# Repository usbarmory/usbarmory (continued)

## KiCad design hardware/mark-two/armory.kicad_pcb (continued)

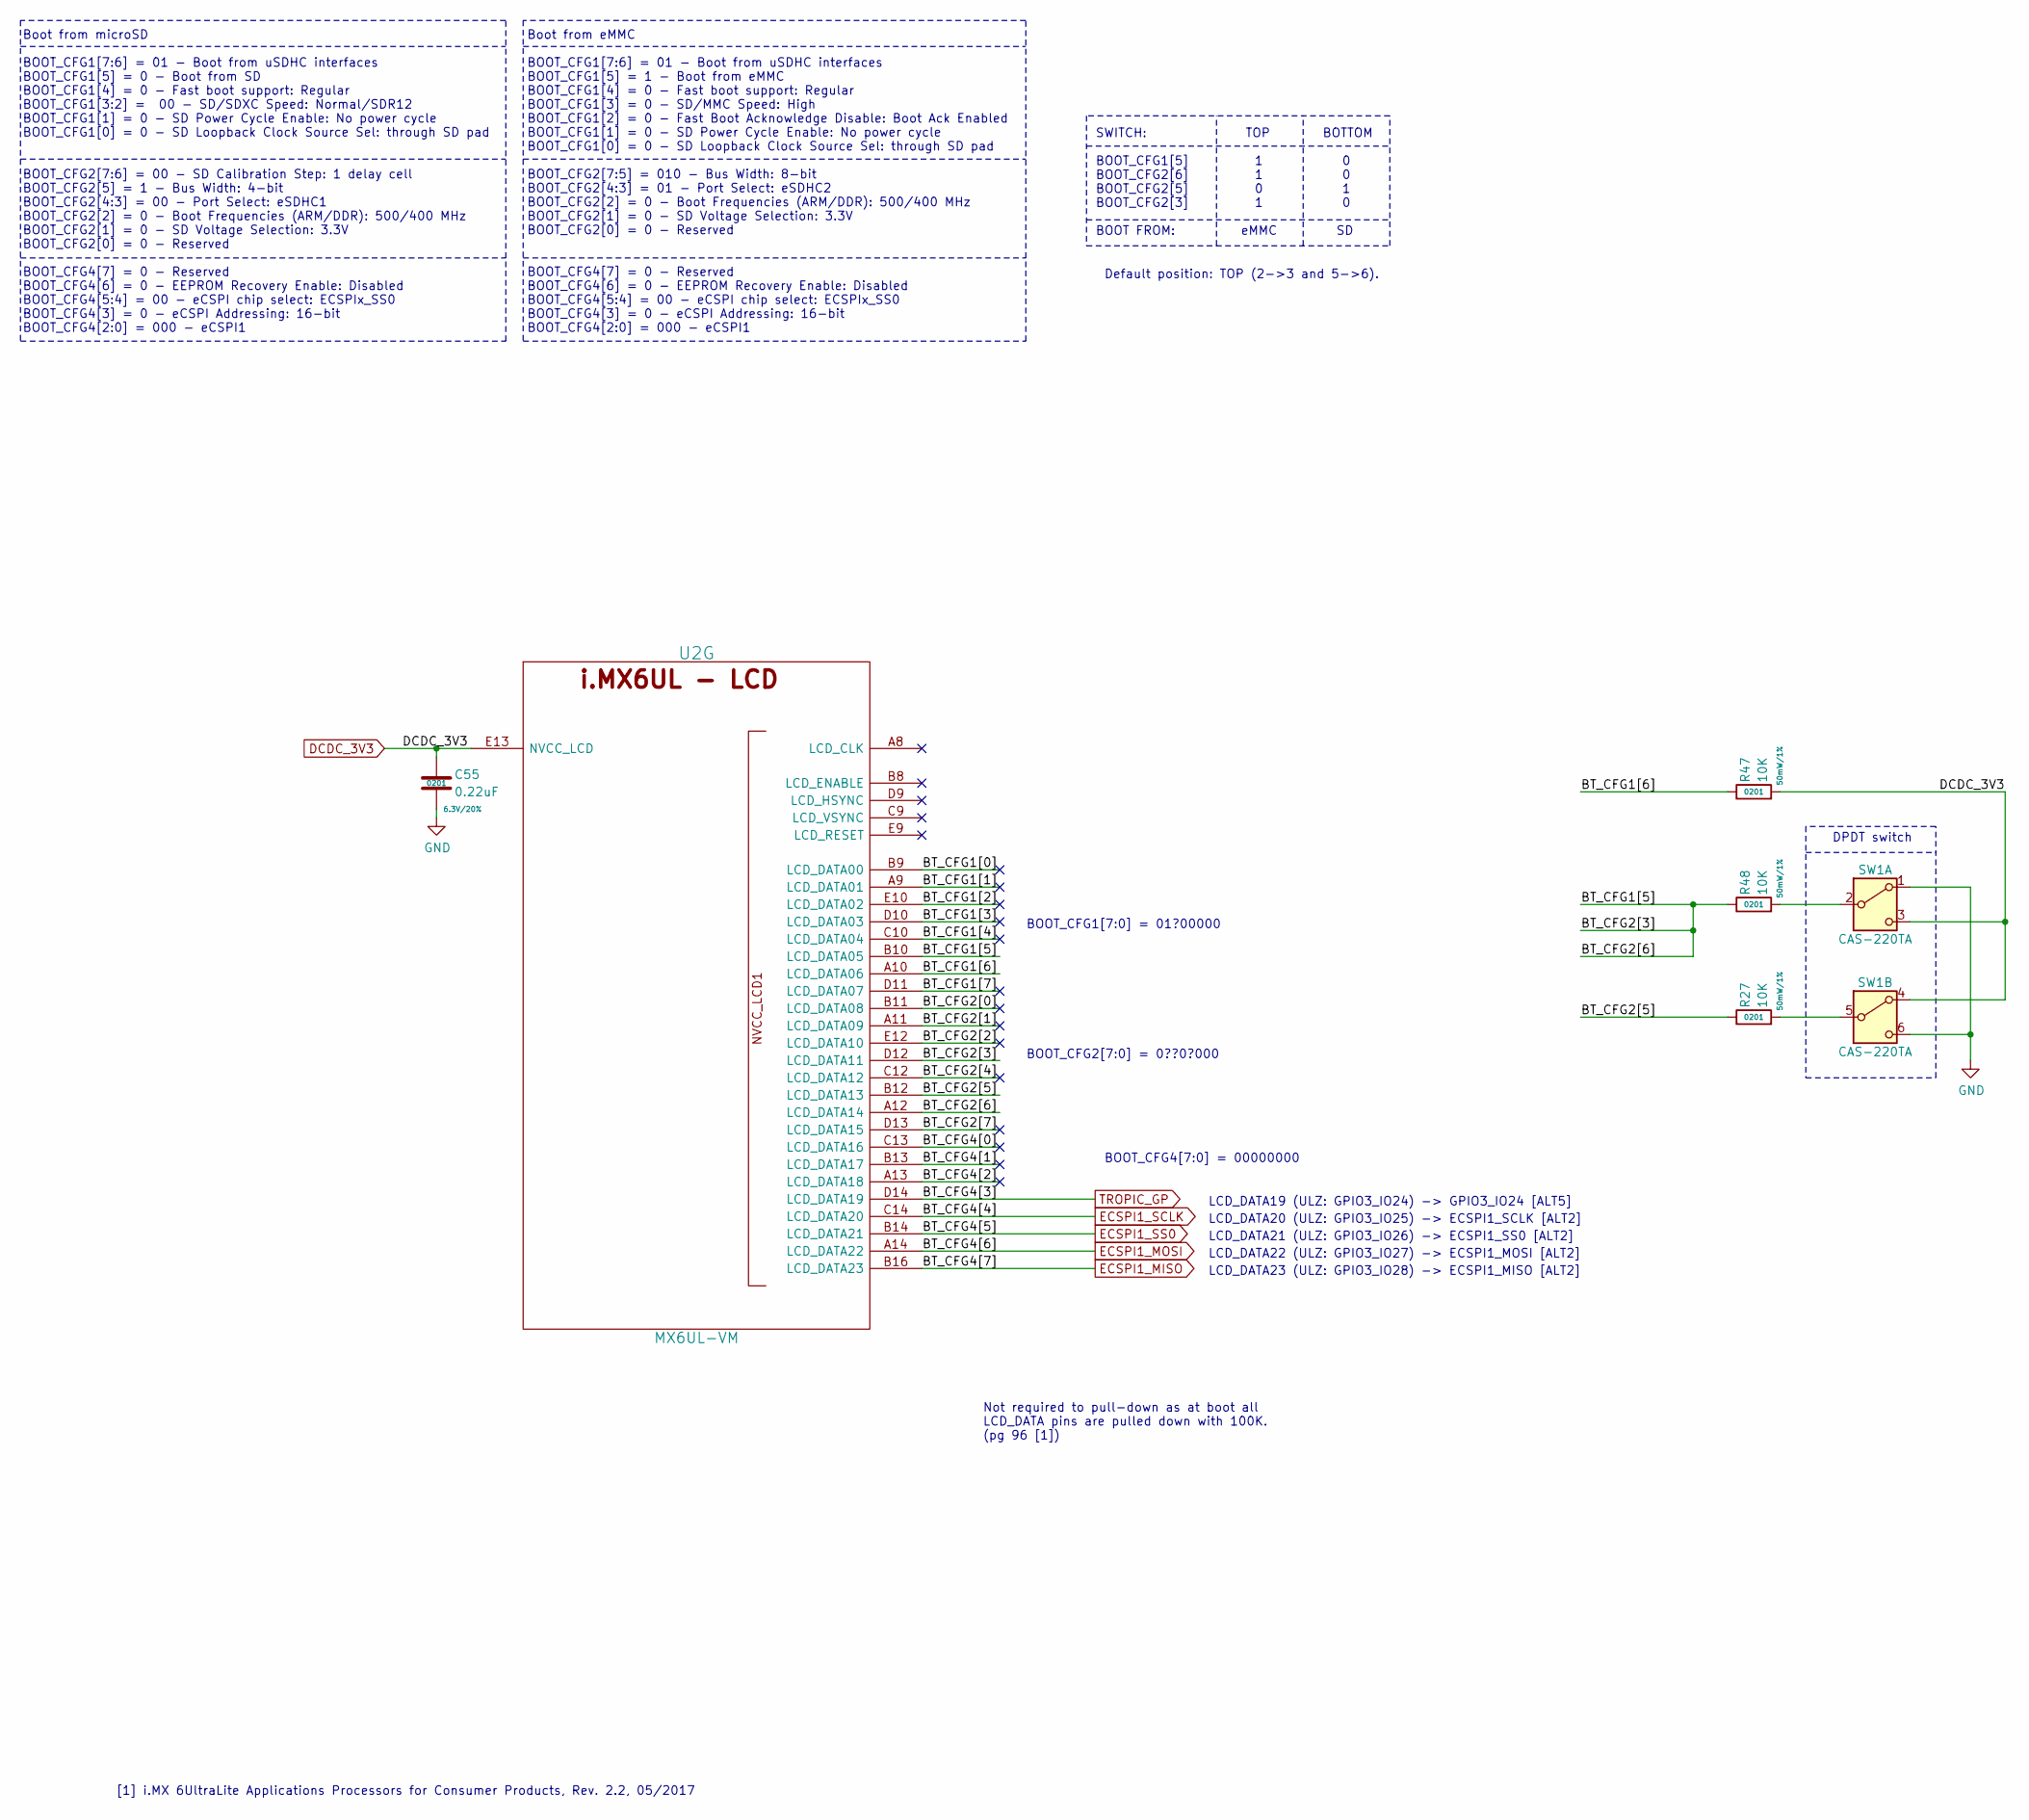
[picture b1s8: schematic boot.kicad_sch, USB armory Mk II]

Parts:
C55: 0.22uF; SM0201; Rating 6.3V/20%; Mfg PN GRM033R60J224ME15D
R27, R47, R48: 10K; SM0201; Rating 50mW/1%; Mfg PN CRCW020110K0JNED
SW1: CAS-220TA; CAS-220-A; Mfg PN CAS-220TA
U2: MX6UL-VM; SOT1534-2; Mfg PN MCIMX6Z0DVM09AB

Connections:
/Boot/BT_CFG1[0]: U2.B9 (LCD_DATA00)
/Boot/BT_CFG1[1]: U2.A9 (LCD_DATA01)
/Boot/BT_CFG1[2]: U2.E10 (LCD_DATA02)
/Boot/BT_CFG1[3]: U2.D10 (LCD_DATA03)
/Boot/BT_CFG1[4]: U2.C10 (LCD_DATA04)
/Boot/BT_CFG1[5]: R48.1, U2.A12 (LCD_DATA14), U2.B10 (LCD_DATA05), U2.D12 (LCD_DATA11)
/Boot/BT_CFG1[6]: R47.1, U2.A10 (LCD_DATA06)
/Boot/BT_CFG1[7]: U2.D11 (LCD_DATA07)
/Boot/BT_CFG2[0]: U2.B11 (LCD_DATA08)
/Boot/BT_CFG2[1]: U2.A11 (LCD_DATA09)
/Boot/BT_CFG2[2]: U2.E12 (LCD_DATA10)
/Boot/BT_CFG2[4]: U2.C12 (LCD_DATA12)
/Boot/BT_CFG2[5]: R27.1, U2.B12 (LCD_DATA13)
/Boot/BT_CFG2[7]: U2.D13 (LCD_DATA15)
/Boot/BT_CFG4[0]: U2.C13 (LCD_DATA16)
/Boot/BT_CFG4[1]: U2.B13 (LCD_DATA17)
/Boot/BT_CFG4[2]: U2.A13 (LCD_DATA18)
DCDC_3V3: C55.1, R47.2, SW1.3 (C), SW1.4 (A), U2.E13 (NVCC_LCD); also elsewhere on the board
ECSPI1_MISO: U2.B16 (LCD_DATA23); also elsewhere on the board
ECSPI1_MOSI: U2.A14 (LCD_DATA22); also elsewhere on the board
ECSPI1_SCLK: U2.C14 (LCD_DATA20); also elsewhere on the board
ECSPI1_SS0: U2.B14 (LCD_DATA21); also elsewhere on the board
GND: C55.2, SW1.1 (A), SW1.6 (C); also elsewhere on the board
unnamed: R48.2, SW1.2 (B)
unnamed: R27.2, SW1.5 (B)
TROPIC_GP: U2.D14 (LCD_DATA19); also elsewhere on the board

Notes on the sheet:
Boot from microSD BOOT_CFG1[7:6] = 01 - Boot from uSDHC interfaces BOOT_CFG1[5] = 0 - Boot from SD BOOT_CFG1[4] = 0 - Fast boot support: Regular BOOT_CFG1[3:2] = 00 - SD/SDXC Speed: Normal/SDR12 BOOT_CFG1[1] = 0 - SD Power Cycle Enable: No power cycle BOOT_CFG1[0] = 0 - SD Loopback Clock Source Sel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
BOOT_CFG4[7:0] = 00000000
Boot from eMMC BOOT_CFG1[7:6] = 01 - Boot from uSDHC interfaces BOOT_CFG1[5] = 1 - Boot from eMMC BOOT_CFG1[4] = 0 - Fast boot support: Regular BOOT_CFG1[3] = 0 - SD/MMC Speed: High BOOT_CFG1[2] = 0 - Fast Boot Acknowledge Disable: Boot Ack Enabled BOOT_CFG1[1] = 0 - SD Power Cycle Enable: No power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
SWITCH: TOP BOTTOM BOOT_CFG1[5] 1 0 BOOT_CFG2[6] 1 0 BOOT_CFG2[5] 0 1 BOOT_CFG2[3] 1 0 BOOT FROM: eMMC SD
DPDT switch
Default position: TOP (2->3 and 5->6).
BOOT_CFG1[7:0] = 01?00000
LCD_DATA21 (ULZ: GPIO3_IO26) -> ECSPI1_SS0 [ALT2]
Not required to pull-down as at boot all LCD_DATA pins are pulled down with 100K. (pg 96 [1])
BOOT_CFG2[7:0] = 0??0?000
LCD_DATA20 (ULZ: GPIO3_IO25) -> ECSPI1_SCLK [ALT2]
LCD_DATA23 (ULZ: GPIO3_IO28) -> ECSPI1_MISO [ALT2]
LCD_DATA22 (ULZ: GPIO3_IO27) -> ECSPI1_MOSI [ALT2]
[1] i.MX 6UltraLite Applications Processors for Consumer Products, Rev. 2.2, 05/2017
LCD_DATA19 (ULZ: GPIO3_IO24) -> GPIO3_IO24 [ALT5]

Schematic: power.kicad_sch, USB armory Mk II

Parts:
C85, C88: 4.7uF; SM0402; Rating 10V/20%; Mfg PN ZRB15XR61A475ME01D
C86, C89, C90, C91, C92, C93, C94, C95, C96, C99, C100, C101: 0.22uF; SM0201; Rating 6.3V/20%; Mfg PN GRM033R60J224ME15D
C87, C98, C103: 22uF; SM0402; Rating 6.3V/20%; Mfg PN CL05A226MQ5N6J8
C97, C102: 10uF; SM0402; Rating 10V/20%; Mfg PN CL05A106MP8NUB8
U2: MX6UL-VM; SOT1534-2; Mfg PN MCIMX6Z0DVM09AB

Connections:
/Power/NVCC_PLL_OUT: C95.1, C97.1, U2.P13 (NVCC_PLL)
/Power/VDD_ARM_CAP: C99.1, C101.1, C103.1, U2.G9 (VDD_ARM_CAP1), U2.G10 (VDD_ARM_CAP2), U2.G11 (VDD_ARM_CAP3), U2.H11 (VDD_ARM_CAP4)
/Power/VDD_SNVS_CAP: C93.1, U2.N12 (VDD_SNVS_CAP)
/Power/VDD_SOC_CAP: C92.1, C94.1, C96.1, C98.1, U2.G8 (VDD_SOC_CAP1), U2.H8 (VDD_SOC_CAP2), U2.J8 (VDD_SOC_CAP3), U2.J11 (VDD_SOC_CAP4), U2.K8 (VDD_SOC_CAP5), U2.K11 (VDD_SOC_CAP6), U2.L8 (VDD_SOC_CAP7), U2.L9 (VDD_SOC_CAP8), U2.L10 (VDD_SOC_CAP9), U2.L11 (VDD_SOC_CAP10)
GND: C85.2, C86.2, C87.2, C88.2, C89.2, C90.2, C91.2, C92.2, C93.2, C94.2, C95.2, C96.2, C97.2, C98.2, C99.2, C100.2, C101.2, C102.2, C103.2, U2.A1 (VSS1), U2.A17 (VSS2), U2.C3 (VSS3), U2.C7 (VSS4), U2.C11 (VSS5), U2.C15 (VSS6), U2.E8 (VSS7), U2.E11 (VSS8), U2.F6 (VSS9), U2.F7 (VSS10), U2.F8 (VSS11), U2.F9 (VSS12), U2.F10 (VSS13), U2.F11 (VSS14), U2.F12 (VSS15), U2.G3 (VSS16), U2.G5 (VSS17), U2.G7 (VSS18), U2.G12 (VSS19), U2.G15 (VSS20), U2.H7 (VSS21), U2.H12 (VSS22), U2.J5 (VSS23), U2.J7 (VSS24), U2.J12 (VSS25), U2.K7 (VSS26), U2.K12 (VSS27), U2.L3 (VSS28), U2.L7 (VSS29), U2.L12 (VSS30), U2.M7 (VSS31), U2.M8 (VSS32), U2.M9 (VSS33), U2.M10 (VSS34), U2.M11 (VSS35), U2.M12 (NGND_KEL0), U2.N3 (VSS36), U2.N5 (VSS37), U2.R3 (VSS38), U2.R5 (VSS39), U2.R7 (VSS40), U2.R11 (VSS41), U2.R16 (VSS42), U2.R17 (VSS43), U2.T14 (VSS44), U2.U1 (VSS45), U2.U14 (VSS46), U2.U17 (VSS47); also elsewhere on the board
LDO2_3V3: C85.1, C86.1, C91.1, U2.N13 (VDD_HIGH_IN), U2.P12 (VDD_SNVS_IN); also elsewhere on the board
VDD_ARM_SOC_IN: C87.1, C88.1, C89.1, C90.1, U2.H9 (VDD_SOC_IN1), U2.H10 (VDD_SOC_IN2), U2.J9 (VDD_SOC_IN3), U2.J10 (VDD_SOC_IN4), U2.K9 (VDD_SOC_IN5), U2.K10 (VDD_SOC_IN6); also elsewhere on the board
VDD_HIGH_CAP: C100.1, C102.1, U2.R14 (VDD_HIGH_CAP1), U2.R15 (VDD_HIGH_CAP2); also elsewhere on the board

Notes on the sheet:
[1] Hardware Development Guide for the i.MX 6UltraLite Application Processor, Rev. 3, 09/2018
VDD_SNVS_IN tied to VDD_HIGH_IN if battery not used. [1] pg 28

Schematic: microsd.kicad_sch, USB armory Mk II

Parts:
C37: 0.22uF; SM0201; Rating 6.3V/20%; Mfg PN GRM033R60J224ME15D
C105: 10uF; SM0402; Rating 10V/20%; Mfg PN CL05A106MP8NUB8
C106: 0.1uF; SM0201; Rating 10V/20%; Mfg PN GRM033R61A104ME15D
J1: microSD slot; MOLEX_503182-1852; Mfg PN 503182-1852
R54: 22R; SM0201; Rating 50mW/1%; Mfg PN CRCW020122R0JNED
R55, R56: 10K; SM0201; Rating 50mW/1%; Mfg PN CRCW020110K0JNED
U2: MX6UL-VM; SOT1534-2; Mfg PN MCIMX6Z0DVM09AB
U12: PUSB3TB6; SOT1358-1; Mfg PN PUSB3TB6AZ
U20, U21: TPD1E10B06; X1SON-2; Mfg PN TPD1E10B06DPYR

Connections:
/microSD/SD1_CLK: J1.5 (CLK), R54.1, U12.2 (CH2)
/microSD/SD1_CLK_R: R54.2, U2.C1 (SD1_CLK)
/microSD/SD1_CMD: J1.3 (CMD), R55.2, U2.C2 (SD1_CMD), U12.6 (CH5)
/microSD/SD1_DATA0: J1.7 (DAT0), R56.2, U2.B3 (SD1_DATA0), U12.7 (CH6)
/microSD/SD1_DATA1: J1.8 (DAT1), U2.B2 (SD1_DATA1), U12.1 (CH1)
/microSD/SD1_DATA2: J1.1 (DATA2), U2.B1 (SD1_DATA2), U12.5 (CH4)
/microSD/SD1_DATA3: J1.2 (CD/DAT3), U2.A2 (SD1_DATA3), U12.3 (CH3)
DCDC_3V3: C105.1, C106.1, J1.4 (VDD), U21.1; also elsewhere on the board
GND: C37.2, C105.2, C106.2, J1.6 (VSS), J1.DT (DETECT), J1.P1 (SHIELD), J1.P2 (SHIELD), J1.P3 (SHIELD), J1.P4 (SHIELD), J1.P5 (SHIELD), U12.4 (GND), U20.2, U21.2; also elsewhere on the board
SD1_CD_B: J1.SW (SWITCH), U20.1; also elsewhere on the board
SD_3V3_1V8: C37.1, R55.1, R56.1, U2.C4 (NVCC_SD1); also elsewhere on the board

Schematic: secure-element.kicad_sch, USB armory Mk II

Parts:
C5, C42, C56, C58: 0.1uF; SM0201; Rating 10V/20%; Mfg PN GRM033R61A104ME15D
R29: 10K; SM0201; Rating 50mW/1%; Mfg PN CRCW020110K0JNED
R30-DNP: 47K; SM0201; Rating 50mW/1%; Mfg PN CRCW020147K0JNED
U4: SE050; SOT1969-1; Mfg PN SE050C1HQ1/Z01SCZ
U13: TR01-P2; QFN-32-1EP_4x4mm_P0.4mm_EP2.65x2.65mm; Mfg PN TR01-C2P-T301

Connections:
DCDC_3V3: C5.1, C42.1, C56.1, C58.1, R29.1, R30-DNP.1, U4.12 (VIN), U13.1 (VCC), U13.11 (VCC), U13.22 (PULLUP), U13.24 (VCC); also elsewhere on the board
ECSPI1_MISO: R30-DNP.2, U13.6 (SDO); also elsewhere on the board
ECSPI1_MOSI: U13.5 (SDI); also elsewhere on the board
ECSPI1_SCLK: U13.7 (SCK); also elsewhere on the board
ECSPI1_SS0: U13.8 (CSN); also elsewhere on the board
GND: C5.2, C42.2, C56.2, C58.2, U4.1 (ISO_14443_LB), U4.14 (ISO_7816_RST_N), U4.17 (ISO_14443_LA), U4.19 (VSS), U4.21 (Thermal), U13.2 (GND), U13.3 (PULLDN), U13.9 (PULLDN), U13.10 (PULLDN), U13.12 (GND), U13.23 (GND), U13.30 (PULLDN), U13.31 (PULLDN), U13.33 (TP); also elsewhere on the board
I2C1_SCL: U4.10 (I2C_SCL); also elsewhere on the board
I2C1_SDA: U4.9 (I2C_SDA); also elsewhere on the board
unnamed: U4.15 (VOUT), U4.18 (VCC)
SE050_ENA: R29.2, U4.11 (ENA); also elsewhere on the board
TROPIC_GP: U13.4 (GPO); also elsewhere on the board

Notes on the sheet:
Do Not Place R30. When installed the board will not boot as it pulls up BOOT_CFG4[7] which needs to be 0 at boot.

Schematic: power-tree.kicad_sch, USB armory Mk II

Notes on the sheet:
VREFDDR
SW1
USB2_VBUS
VBUS
RX1-
GND
PMIC
LED blue
SoC
DCDC_3V3
RX2-
VDDA_ADC_3P3
Secure Element 2
RX1+
VDD_HIGH_CAP
CC2
TX1-
VDD_SNVS_IN
EMMC_1V8
Type-C PLUG
USB_VBUS
A12
u-blox ANNA-B112
B10
VLDO3
DDR3L 512 MB / 1 GB
VDD_SOC_IN
USB1_VBUS
FUSB303 - RCPT
NVCC_LCD
VLDO2
unused
SBU1
VCC
Bluetooth module
push-push slot
NVCC_NAND
B11
DDR
LED white

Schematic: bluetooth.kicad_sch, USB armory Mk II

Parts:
C104: 0.1uF; SM0201; Rating 10V/20%; Mfg PN GRM033R61A104ME15D
TP8, TP9: TestPoint; TP
U11: ANNA-B112; Mfg PN ANNA-B112-01B

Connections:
/Bluetooth/ANT_INT: U11.5 (ANT_INT), U11.6 (ANT)
/Bluetooth/ANT_PCB: U11.1 (ANT_PCB)
BT_RESET_B: U11.12 (~RESET); also elsewhere on the board
BT_SWDCLK: U11.39 (SWD_CLK); also elsewhere on the board
BT_SWDIO: U11.40 (SWD_IO); also elsewhere on the board
BT_SWITCH_1: U11.30 (GREEN/SWITCH_1); also elsewhere on the board
BT_SWITCH_2: U11.38 (SWITCH_2); also elsewhere on the board
BT_UART_CTS: U11.35 (UART_CTS); also elsewhere on the board
BT_UART_DSR: U11.26 (UART_DSR); also elsewhere on the board
BT_UART_DTR: U11.25 (UART_DTR); also elsewhere on the board
BT_UART_RTS: U11.34 (UART_RTS); also elsewhere on the board
BT_UART_RX: TP9.1 (1_1), U11.19 (UART_TXD); also elsewhere on the board
BT_UART_TX: TP8.1 (1_1), U11.20 (UART_RXD); also elsewhere on the board
DCDC_3V3: C104.1, U11.9 (VCC); also elsewhere on the board
GND: C104.2, U11.4 (GND), U11.7 (GND), U11.8 (GND), U11.10 (GND), U11.11 (GND), U11.17 (XL1), U11.18 (XL2), U11.32 (GND), U11.33 (GND), U11.41 (GND), U11.42 (GND), U11.43 (GND), U11.44 (GND), U11.46 (GND), U11.47 (GND), U11.48 (GND), U11.49 (GND), U11.50 (GND), U11.51 (GND), U11.52 (GND); also elsewhere on the board

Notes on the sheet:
It has been witnessed that the ANNA-B112 can be back-powered via UART pins. To turn completelly off the module all the interfaces pins should be kept low.
RESET_N: 13 kOhm internal pull-up. [2] pg 28
There is no strict requirement of adding bypass capacitance to the supply net close to the module. But depending on the layout of the supply net and other consumers on the same net, bypass capacitors might still be beneficial. [1] pg 40
Integrated antenna module placed - in the corner of the PCB: ANT_PCB -> GND pattern ANT_GND_x -> NC - on the side of the PCB: ANT_PCB -> NC ANT_GND_x -> GND [1] pg 14
When using internal oscillator XL1 and XL2 should be connected to ground ([1] pg 11).
[1] ANNA-B112 - System Integration Manual (UBX-18009821-R07)
[2] ANNA-B112 - Data Sheet (UBX-18011707-R04)
NFC_1 and NFC_2: floating Not found any reference, but should be safe as they are also GPIO.
Use internal antenna.

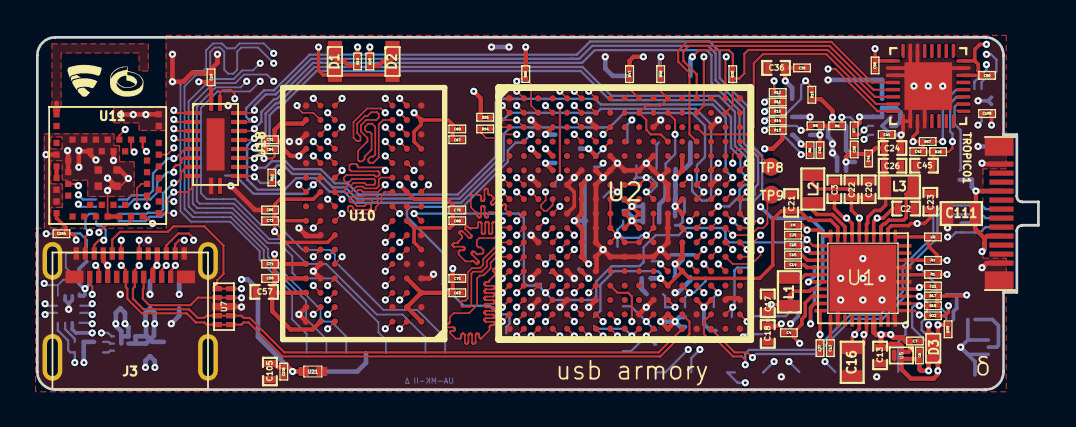
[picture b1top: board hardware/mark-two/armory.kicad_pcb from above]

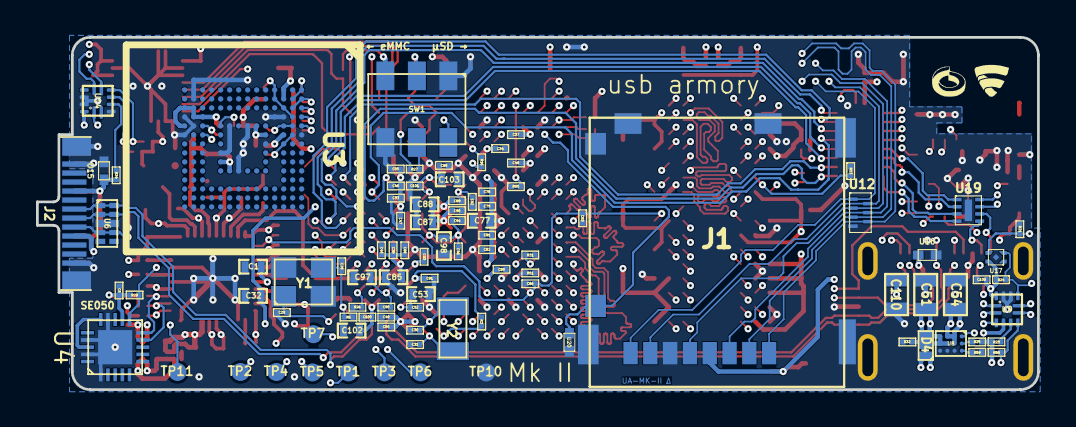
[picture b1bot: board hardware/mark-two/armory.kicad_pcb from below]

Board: 6 copper layers, 55.6 x 19.6 mm, 198 parts (98 on the bottom side), 177 nets.

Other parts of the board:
FSC_LOGO_NO_TEXT_SMALL: G***; FSC_LOGO_NO_TEXT_SMALL
FSC_LOGO_NO_TEXT_SMALL#2: G***; FSC_LOGO_NO_TEXT_SMALL
R30: 47K; SM0201
Ref**: Val**; IP_LOGO_NO_TEXT_SMALL
Ref**#2: Val**; IP_LOGO_NO_TEXT_SMALL

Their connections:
DCDC_3V3: R30.1; also elsewhere on the board
ECSPI1_MISO: R30.2; also elsewhere on the board

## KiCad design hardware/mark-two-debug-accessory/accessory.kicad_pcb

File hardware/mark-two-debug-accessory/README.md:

USB armory Mk II debug accessory
================================

The USB armory is an open source hardware design, implementing a flash drive
sized computer.

The USB armory Mk II exposes a USB Type-C receptacle, which allows through the
so called USB-C 'debug accessory mode' to route analog/debug signals over its
connector, the USB armory Mk II design leverages on this to break out UART,
SPI, I²C, CAN (pre-transceiver), GPIOs connections to/from its application
processor.

The debug accessory board allows to access UART and GPIO signals through USB,
without requiring probes, through an FTDI FT4232H. This allows, for example,
access to the USB armory Mk II serial console without wires or probes, natively
using only USB cables. All other interfaces can be accessed through dedicated
breakout through holes.

This repository is aimed towards developers, if you wish to purchase a USB
armory board please see the [USB armory documentation](https://github.com/usbarmory/usbarmory/wiki).

PCB Information
===============

2 layers, 0.80mm thickness, top only components  
Outer layers 0.5 oz base copper foil  
Inner layers   1 oz base copper foil  
width (X) 45.65 mm, height (Y) 25.90 mm  
Red soldermask, white component legend

[Bill of materials](https://usbarmory.github.io/BOM/usbarmory-mark-two-debug-accessory.html)

DRC information
---------------

Minimum track width:            0.127 mm  
Minimum via diameter:           0.450 mm  
Outer layer track width:        0.127 mm  
Outer layer isolation distance: 0.127 mm  
Outer layer annular ring:       0.100 mm  
Smallest final hole (plated):   0.150 mm

Errata
------

The silkscreen labels for `3.3V` and `5V` are inverted on all rev v1 PCBs, see
this [issue](https://github.com/usbarmory/usbarmory/issues/68).

USB armory Mk II debug I/Os
===========================

*NOTE*: the connection between the debug accessory and the target is supported
only with the same orientation for both top layers (side with components for
the accessory, side with LEDs for the USB armory).

The following table summarizes the available configurations on the USB armory
Mk II through debug accessory mode, which are exposed on its Type-C receptacle
port.

|  USB-C pin   | MUX mode ALT0 | MUX mode ALT8 | MUX mode ALT2 | MUX mode ALT5 |
|:-------------|---------------|---------------|---------------|---------------|
| SSTXp1 (A2)  | UART2_TX      | ECSPI3_SSO¹   | I2C4_SCL¹     | GPIO1_IO20    |
| SSTXn1 (A3)  | UART2_RX      | ECSPI3_SCLK¹  | I2C4_SDA¹     | GPIO1_IO21    |
| SSRXp1 (B11) | UART2_RTS_B   | ECSPI3_MISO¹  | FLEXCAN2_RX¹  | GPIO1_IO23    |
| SSRXn1 (B10) | UART2_CTS_B   | ECSPI3_MOSI¹  | FLEXCAN2_TX¹  | GPIO1_IO22    |
| SSRXp2 (A11) | UART4_TX      | ECSPI2_SCLK   | I2C1_SCL      | GPIO1_IO28    |
| SSTXn2 (B3)  | UART4_RX      | ECSPI2_SSO    | I2C1_SDA      | GPIO1_IO29    |
| SSRXn2 (A10) | UART5_TX~     | ECSPI2_MOSI   | I2C2_SCL      | GPIO1_IO30    |
| SSTXp2 (B2)  | UART5_RX~     | ECSPI2_MISO   | I2C2_SDA      | GPIO1_IO31    |

¹ Only on USB armory Mk II boards mounting i.MX6UL SoC, not available on
  versions mounting the i.MX6ULZ.

Serial console
--------------

When running the [USB armory Debian base image](https://github.com/usbarmory/usbarmory-debian-base_image/releases)
the serial console (UART2) can be accessed, with the debug accessory jumper set to UART
position, as follows (example on Linux host with picocom):

```
picocom -b 115200 -eb /dev/ttyUSB2 --imap lfcrlf
```

Debug accessory jumper settings
===============================

Power source
------------

The debug accessory always acts as a power source and is meant to be connected
exclusively to the USB armory Mk II Type-C receptacle port. The USB armory Mk
II Type-C can be safely plugged on a different receptacle as the board can
handle two power sources simultaneously.

It is not recommended to connect the debug accessory to anything other than the
USB armory Mk II, however in case this happens compliant Type-C receptacles
should handle the situation gracefully¹ without concerns.

¹ USB Type-C Cable and Connector Specification (1.3, 2017-07-14):
  "Legacy hosts/chargers that by default source VBUS when connected using any
  legacy USB connector (Standard-A, Micro-B, etc.) to USB Type-C cable or adapter
  are exempted from these two requirements."

I/O mode
--------

The GPIO and UART functions can be used directly using the FTDI FT4232H USB
interface accessible on the Micro USB Type-B connector, all other modes can be
accessed using the exposed breakout through holes.

The following table illustrates the required jumper positions and interfaces
for each available I/O mode.

| Mode  | GPIO¹ | Interface
|:------|-------|-----------------------------------|
| GPIO  |  GPIO | FTDI MPSSE mode on [A,B]DBUS[4-7] |
| UART2 | !GPIO | FTDI RS232 mode on CDBUS[0-3]     |
| UART4 | !GPIO | FTDI RS232 mode on BDBUS[0-1]     |
| UART5 | !GPIO | FTDI RS232 mode on ADBUS[0-1]     |
| SPI2  |  N/A² | through holes: A11, B3, A10, B2   |
| SPI3  |  N/A² | through holes: A2,  A3, B11, B10  |
| I2C1  |  N/A² | through holes: A11, B3            |
| I2C2  |  N/A² | through holes: A10, B2            |
| I2C4  |  N/A² | through holes: A2,  A3            |
| CAN2  |  N/A² | through holes: B11, B10           |

¹ The GPIO header position refers to termination either of the two pins facing
  the "GPIO" label (GPIO position, pins towards positions 3 and 2) or the
  opposite position (!GPIO position, pins towards positions 2 and 1).

² Any position can be used as the FTDI is not used in such mode.

Pin assignment: GPIO
====================

|  USB-C pin   | i.MX6UL pin | FTDI pin | FTDI MPSSE |
|:-------------|-------------|----------|------------|
| SSTXp1 (A2)  | GPIO1_IO20  | BDBUS6   | #B GPIOL2  |
| SSTXn1 (A3)  | GPIO1_IO21  | BDBUS7   | #B GPIOL3  |
| SSRXp1 (B11) | GPIO1_IO23  | BDBUS5   | #B GPIOL1  |
| SSRXn1 (B10) | GPIO1_IO22  | BDBUS4   | #B GPIOL0  |
| SSRXp2 (A11) | GPIO1_IO28  | ADBUS4   | #A GPIOL0  |
| SSTXn2 (B3)  | GPIO1_IO29  | ADBUS7   | #A GPIOL3  |
| SSRXn2 (A10) | GPIO1_IO30  | ADBUS5   | #A GPIOL1  |
| SSTXp2 (B2)  | GPIO1_IO31  | ADBUS6   | #A GPIOL2  |

Pin assignment: UART2
=====================

|  USB-C pin   | i.MX6UL pin  | FTDI pin | FTDI MPSSE |
|:-------------|--------------|----------|------------|
| SSTXp1 (A2)  | UART2_TX     | CDBUS1   | #C RXD     |
| SSTXn1 (A3)  | UART2_RX     | CDBUS0   | #C TXD     |
| SSRXp1 (B11) | UART2_RTS_B¹ | CDBUS3   | #C CTS     |
| SSRXn1 (B10) | UART2_CTS_B¹ | CDBUS2   | #C RTS     |

¹ On USB armory Mk II rev. β see the [related errata](https://github.com/usbarmory/usbarmory/wiki/Errata-(Mk-II)#errata-inverted-uart-rtscts-signals-resolved-with-workaround).

Pin assignment: UART4
=====================

|  USB-C pin   | i.MX6UL pin | FTDI pin | FTDI MPSSE |
|:-------------|-------------|----------|------------|
| SSRXp2 (A11) | UART4_TX    | BDBUS1   | #B RXD     |
| SSTXn2 (B3)  | UART4_RX    | BDBUS0   | #B TXD     |

Pin assignment: UART5
=====================

|  USB-C pin   | i.MX6UL pin | FTDI pin | FTDI MPSSE |
|:-------------|-------------|----------|------------|
| SSRXn2 (A10) | UART5_TX    | ADBUS1   | #A RXD     |
| SSTXp2 (B2)  | UART5_RX    | ADBUS0   | #A TXD     |

Physical access: UART2
======================

When no debug accessory is available, the serial console (UART2) can be also
accessed with a USB-C plug breakout and a USB to 3.3 TTL serial cable with the
following configuration.

|  PIN   | Config          |
|:-------|-----------------|
| A4, A5 | 56 kOhm         |
| B4, B5 | 56 kOhm         |
| A2, A3 | 3.3V UART TX/RX |
| A4     | 5V              |
| A1     | GND             |

License
=======

USB armory | https://github.com/usbarmory/usbarmory  
Copyright (c) The USB armory authors

This is an open hardware design licensed under the terms of the CERN Open
Hardware Licence (OHL) v1.2.

You may redistribute and modify this documentation under the terms of the CERN
OHL v.1.2 (http://ohwr.org/cernohl). This documentation is distributed WITHOUT
ANY EXPRESS OR IMPLIED WARRANTY, INCLUDING OF MERCHANTABILITY, SATISFACTORY
QUALITY AND FITNESS FOR A PARTICULAR PURPOSE. Please see the CERN OHL v.1.2 for
applicable conditions.

The following exceptions apply:

- `../lib.snapeda`: all files in this directory are imported or modified
  from SnapEDA symbols and footprints, therefore the license at
  https://www.snapeda.com/about/FAQ/#license applies.

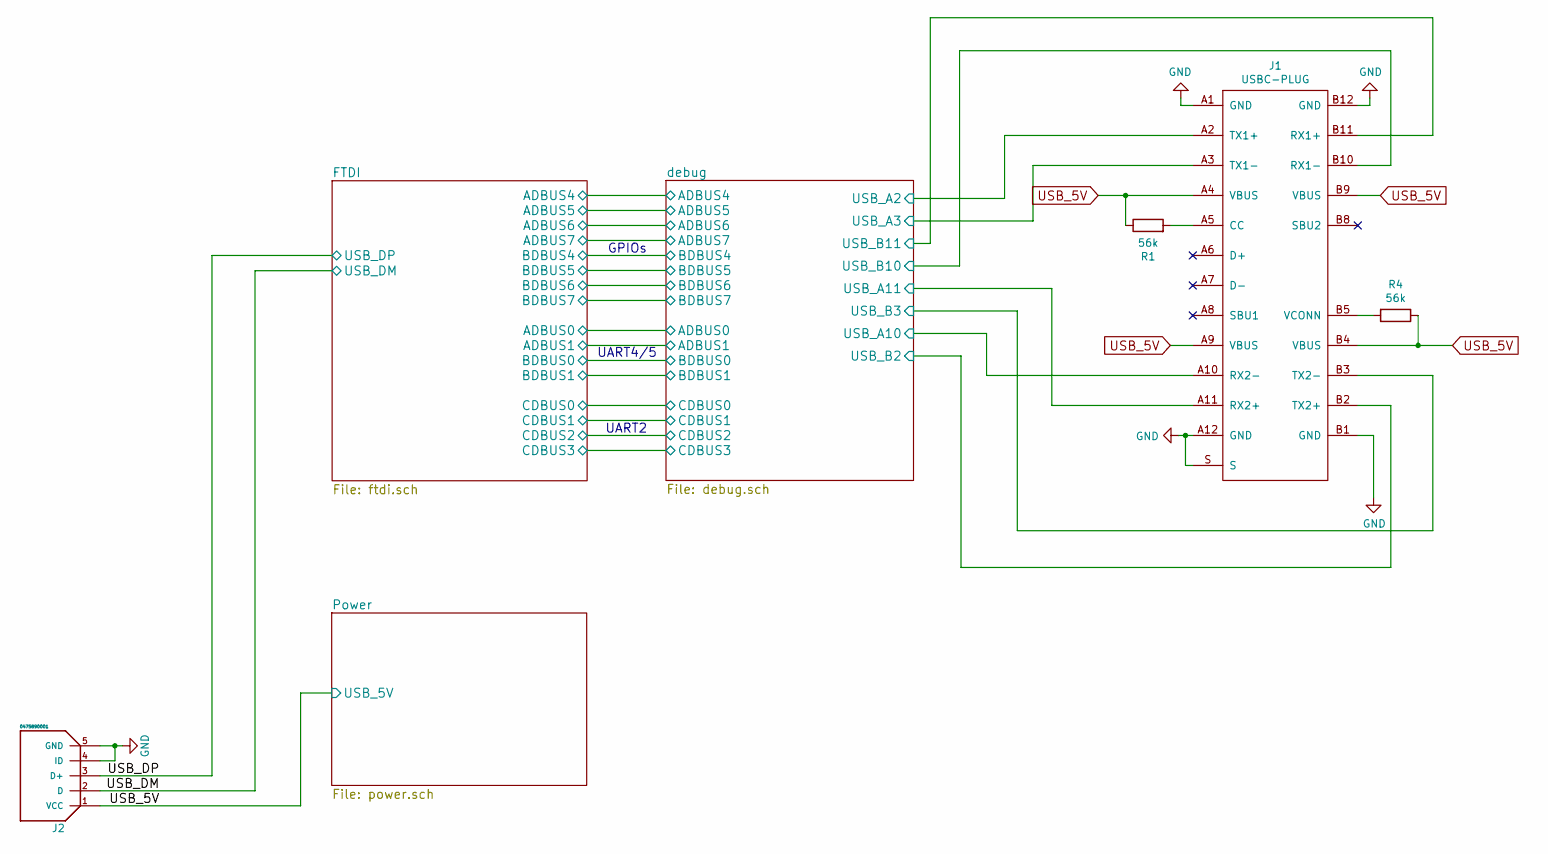
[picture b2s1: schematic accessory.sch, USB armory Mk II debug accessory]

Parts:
J1: USBC-PLUG; WURTH_632712000011; Mfg PN 632712000011
J2: 0475890001; MOLEX_0475890001; Mfg PN 0475890001
R1, R4: 56k; SM0603; Mfg PN MCT06030C5602FP500

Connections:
/USB_DM: J2.2 (D); also elsewhere on the board
/USB_DP: J2.3 (D+); also elsewhere on the board
/debug/USB_A2: J1.A2 (TX1+); also elsewhere on the board
/debug/USB_A3: J1.A3 (TX1-); also elsewhere on the board
/debug/USB_A10: J1.A10 (RX2-); also elsewhere on the board
/debug/USB_A11: J1.A11 (RX2+); also elsewhere on the board
/debug/USB_B2: J1.B2 (TX2+); also elsewhere on the board
/debug/USB_B3: J1.B3 (TX2-); also elsewhere on the board
/debug/USB_B10: J1.B10 (RX1-); also elsewhere on the board
/debug/USB_B11: J1.B11 (RX1+); also elsewhere on the board
GND: J1.A1 (GND), J1.A12 (GND), J1.B1 (GND), J1.B12 (GND), J1.S, J2.4 (ID), J2.5 (GND); also elsewhere on the board
unnamed: J1.A5 (CC), R1.2
unnamed: J1.B5 (VCONN), R4.2
USB_5V: J1.A4 (VBUS), J1.A9 (VBUS), J1.B4 (VBUS), J1.B9 (VBUS), J2.1 (VCC), R1.1, R4.1; also elsewhere on the board

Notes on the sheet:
GPIOs
UART4/5
UART2

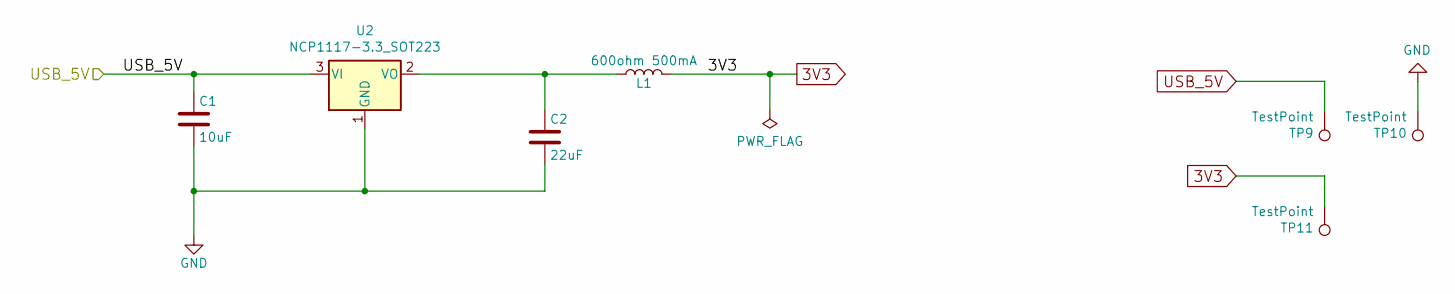
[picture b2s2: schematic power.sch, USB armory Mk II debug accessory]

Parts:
C1: 10uF; SM0603; Mfg PN C1608X5R1A106M080AC
C2: 22uF; SM0603; Mfg PN C1608X5R1A226M080AC
L1: 600ohm 500mA; SM0603; Mfg PN BLM18AG601SN1D
TP9, TP10, TP11: TestPoint; CONN_1
U2: NCP1117-3.3_SOT223; SOT-223; Mfg PN NCP1117ST33T3G

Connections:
3V3: L1.2, TP11.1; also elsewhere on the board
GND: C1.2, C2.2, TP10.1, U2.1 (GND); also elsewhere on the board
unnamed: C2.1, L1.1, U2.2 (VO)
USB_5V: C1.1, TP9.1, U2.3 (VI); also elsewhere on the board

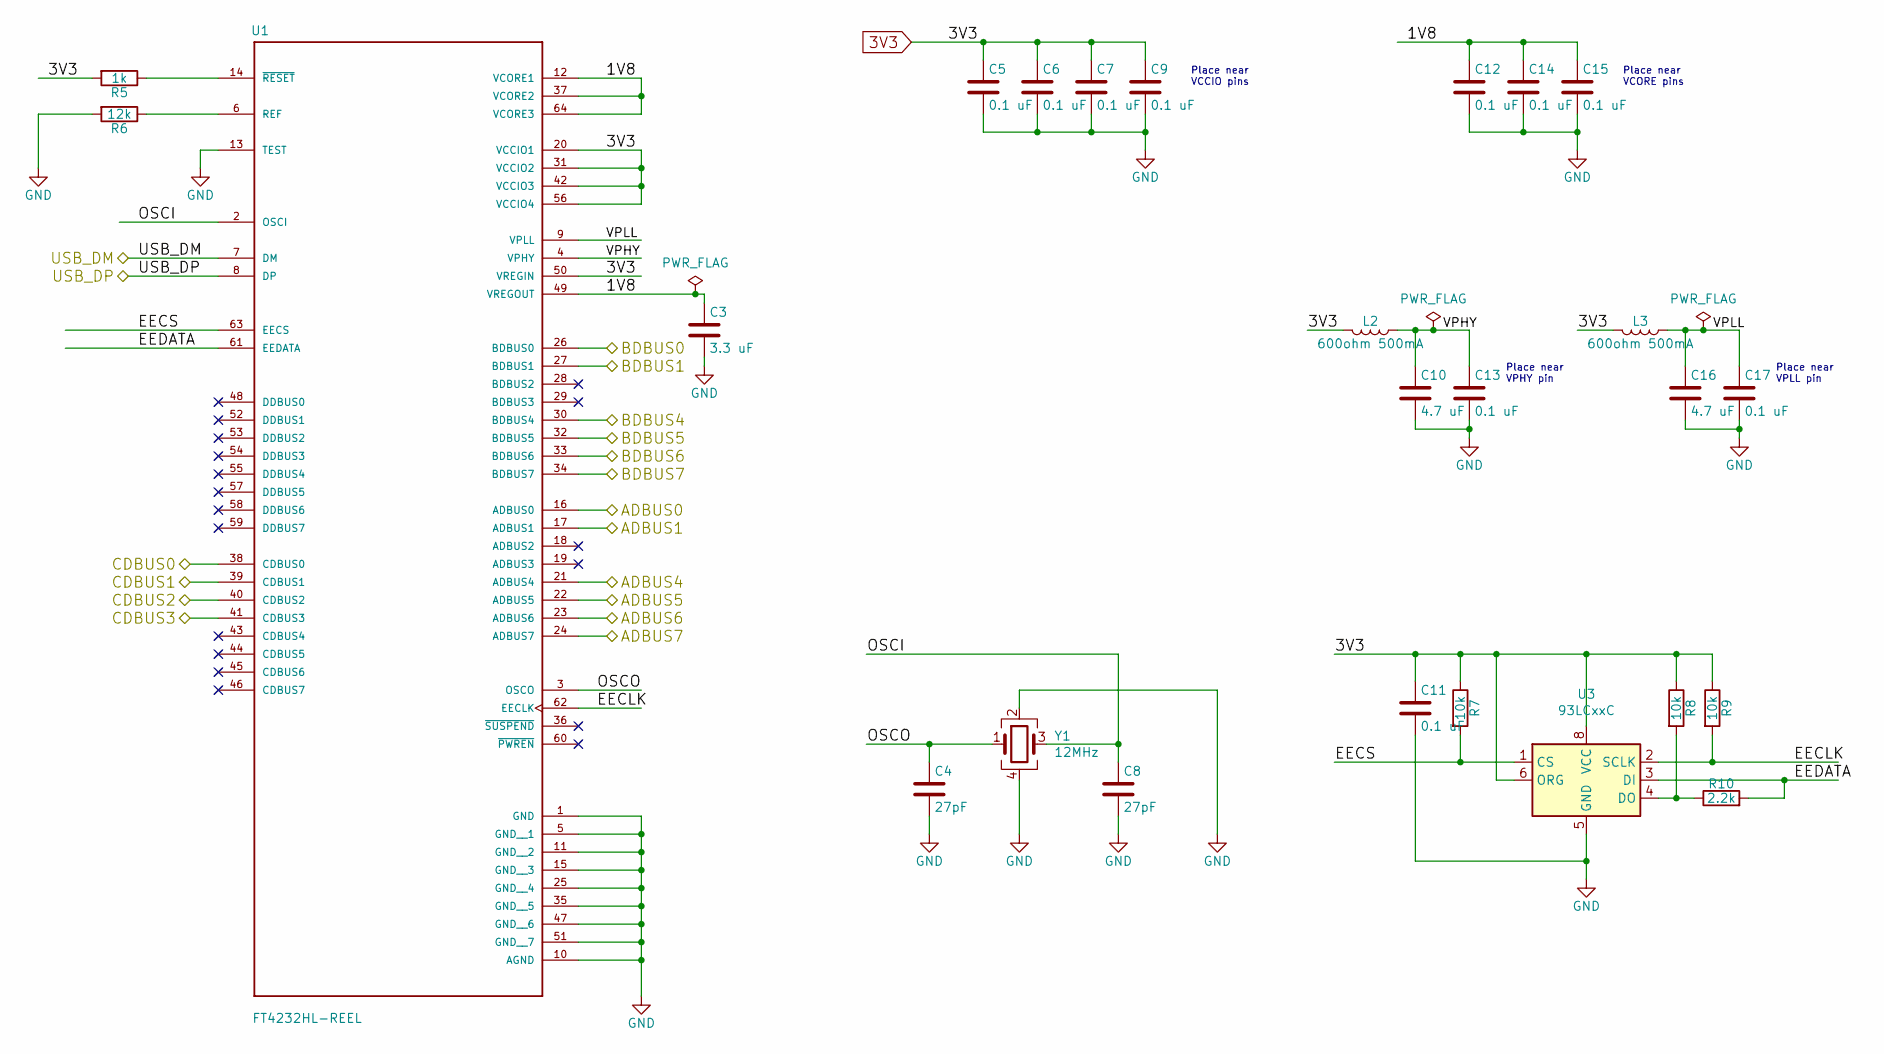
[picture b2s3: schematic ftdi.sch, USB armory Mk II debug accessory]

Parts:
C3: 3.3 uF; SM0603; Mfg PN C1608X5R1C335K080AC
C4, C8: 27pF; SM0603; Mfg PN GRM1885C1H270FA01D
C5, C6, C7, C9, C11, C12, C13, C14, C15, C17: 0.1 uF; SM0603; Mfg PN C1608X7R1E104K080AA
C10, C16: 4.7 uF; SM0603; Mfg PN CGB3B1X5R1A475M055AC
L2, L3: 600ohm 500mA; SM0603; Mfg PN BLM18AG601SN1D
R5: 1k; SM0603; Mfg PN RCA06031K00FKEAHP
R6: 12k; SM0603; Mfg PN CRCW060312K0FKEAC
R7, R8, R9: 10k; SM0603; Mfg PN CRCW060310K0FKEA
R10: 2.2k; SM0603; Mfg PN RCS06032K20JNEA
U1: FT4232HL-REEL; QFP50P1200X1200X160-64N; Mfg PN FT4232HL-REEL
U3: 93LCxxC; 8L_SOIC_Narrow_3_90_SN_C04-057C; Mfg PN 93LC56C-I/SN
Y1: 12MHz; TXC-3.2x2.5; Mfg PN 7M-12.000MAAJ-T

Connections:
3V3: C5.1, C6.1, C7.1, C9.1, C11.1, L2.1, L3.1, R5.2, R7.1, R8.1, R9.1, U1.20 (VCCIO1), U1.31 (VCCIO2), U1.42 (VCCIO3), U1.50 (VREGIN), U1.56 (VCCIO4), U3.6 (ORG), U3.8 (VCC); also elsewhere on the board
/FTDI/1V8: C3.1, C12.1, C14.1, C15.1, U1.12 (VCORE1), U1.37 (VCORE2), U1.49 (VREGOUT), U1.64 (VCORE3)
/FTDI/ADBUS0: U1.16 (ADBUS0); also elsewhere on the board
/FTDI/ADBUS1: U1.17 (ADBUS1); also elsewhere on the board
/FTDI/ADBUS4: U1.21 (ADBUS4); also elsewhere on the board
/FTDI/ADBUS5: U1.22 (ADBUS5); also elsewhere on the board
/FTDI/ADBUS6: U1.23 (ADBUS6); also elsewhere on the board
/FTDI/ADBUS7: U1.24 (ADBUS7); also elsewhere on the board
/FTDI/BDBUS0: U1.26 (BDBUS0); also elsewhere on the board
/FTDI/BDBUS1: U1.27 (BDBUS1); also elsewhere on the board
/FTDI/BDBUS4: U1.30 (BDBUS4); also elsewhere on the board
/FTDI/BDBUS5: U1.32 (BDBUS5); also elsewhere on the board
/FTDI/BDBUS6: U1.33 (BDBUS6); also elsewhere on the board
/FTDI/BDBUS7: U1.34 (BDBUS7); also elsewhere on the board
/FTDI/CDBUS0: U1.38 (CDBUS0); also elsewhere on the board
/FTDI/CDBUS1: U1.39 (CDBUS1); also elsewhere on the board
/FTDI/CDBUS2: U1.40 (CDBUS2); also elsewhere on the board
/FTDI/CDBUS3: U1.41 (CDBUS3); also elsewhere on the board
/FTDI/EECLK: R9.2, U1.62 (EECLK), U3.2 (SCLK)
/FTDI/EECS: R7.2, U1.63 (EECS), U3.1 (CS)
/FTDI/EEDATA: R10.2, U1.61 (EEDATA), U3.3 (DI)
/FTDI/OSCI: C8.1, U1.2 (OSCI), Y1.3
/FTDI/OSCO: C4.1, U1.3 (OSCO), Y1.1
/FTDI/VPHY: C10.1, C13.1, L2.2, U1.4 (VPHY)
/FTDI/VPLL: C16.1, C17.1, L3.2, U1.9 (VPLL)
/USB_DM: U1.7 (DM); also elsewhere on the board
/USB_DP: U1.8 (DP); also elsewhere on the board
GND: C3.2, C4.2, C5.2, C6.2, C7.2, C8.2, C9.2, C10.2, C11.2, C12.2, C13.2, C14.2, C15.2, C16.2, C17.2, R6.2, U1.1 (GND), U1.5 (GND__1), U1.10 (AGND), U1.11 (GND__2), U1.13 (TEST), U1.15 (GND__3), U1.25 (GND__4), U1.35 (GND__5), U1.47 (GND__6), U1.51 (GND__7), U3.5 (GND), Y1.2, Y1.4; also elsewhere on the board
unnamed: R5.1, U1.14 (~RESET~)
unnamed: R6.1, U1.6 (REF)
unnamed: R8.2, R10.1, U3.4 (DO)

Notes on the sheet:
Place near VCORE pins
Place near VCCIO pins
Place near VPLL pin
Place near VPHY pin

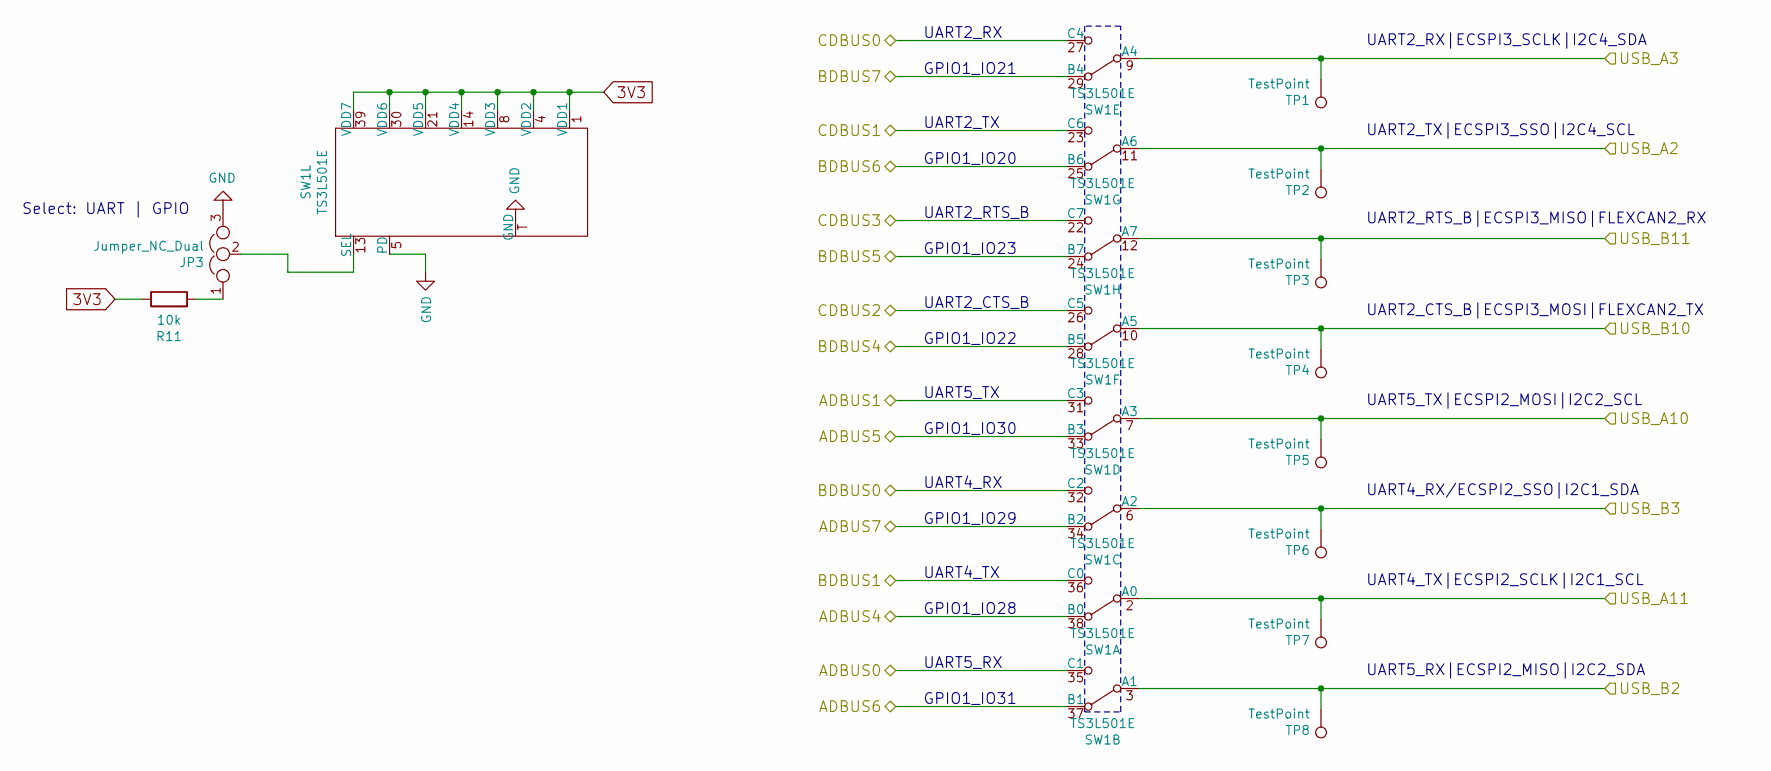
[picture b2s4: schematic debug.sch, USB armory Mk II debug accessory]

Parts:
JP3: Jumper_NC_Dual; SIL-3; Mfg PN 68000-103HLF
R11: 10k; SM0603; Mfg PN CRCW060310K0FKEA
SW1: TS3L501E; R-PWQFN-N42
TP1, TP2, TP3, TP4, TP5, TP6, TP7, TP8: TestPoint; CONN_1

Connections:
3V3: R11.1, SW1.1 (VDD1), SW1.4 (VDD2), SW1.8 (VDD3), SW1.14 (VDD4), SW1.21 (VDD5), SW1.30 (VDD6), SW1.39 (VDD7); also elsewhere on the board
/FTDI/ADBUS0: SW1.35 (C1); also elsewhere on the board
/FTDI/ADBUS1: SW1.31 (C3); also elsewhere on the board
/FTDI/ADBUS4: SW1.38 (B0); also elsewhere on the board
/FTDI/ADBUS5: SW1.33 (B3); also elsewhere on the board
/FTDI/ADBUS6: SW1.37 (B1); also elsewhere on the board
/FTDI/ADBUS7: SW1.34 (B2); also elsewhere on the board
/FTDI/BDBUS0: SW1.32 (C2); also elsewhere on the board
/FTDI/BDBUS1: SW1.36 (C0); also elsewhere on the board
/FTDI/BDBUS4: SW1.28 (B5); also elsewhere on the board
/FTDI/BDBUS5: SW1.24 (B7); also elsewhere on the board
/FTDI/BDBUS6: SW1.25 (B6); also elsewhere on the board
/FTDI/BDBUS7: SW1.29 (B4); also elsewhere on the board
/FTDI/CDBUS0: SW1.27 (C4); also elsewhere on the board
/FTDI/CDBUS1: SW1.23 (C6); also elsewhere on the board
/FTDI/CDBUS2: SW1.26 (C5); also elsewhere on the board
/FTDI/CDBUS3: SW1.22 (C7); also elsewhere on the board
/debug/USB_A2: SW1.11 (A6), TP2.1; also elsewhere on the board
/debug/USB_A3: SW1.9 (A4), TP1.1; also elsewhere on the board
/debug/USB_A10: SW1.7 (A3), TP5.1; also elsewhere on the board
/debug/USB_A11: SW1.2 (A0), TP7.1; also elsewhere on the board
/debug/USB_B2: SW1.3 (A1), TP8.1; also elsewhere on the board
/debug/USB_B3: SW1.6 (A2), TP6.1; also elsewhere on the board
/debug/USB_B10: SW1.10 (A5), TP4.1; also elsewhere on the board
/debug/USB_B11: SW1.12 (A7), TP3.1; also elsewhere on the board
GND: JP3.3, SW1.5 (PD), SW1.T (GND); also elsewhere on the board
unnamed: JP3.1, R11.2
unnamed: JP3.2, SW1.13 (SEL)

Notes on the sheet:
UART2_CTS_B|ECSPI3_MOSI|FLEXCAN2_TX
UART5_TX|ECSPI2_MOSI|I2C2_SCL
UART4_RX/ECSPI2_SSO|I2C1_SDA
UART4_TX|ECSPI2_SCLK|I2C1_SCL
UART5_RX|ECSPI2_MISO|I2C2_SDA
UART2_RTS_B|ECSPI3_MISO|FLEXCAN2_RX
UART2_TX|ECSPI3_SSO|I2C4_SCL
UART2_RX|ECSPI3_SCLK|I2C4_SDA
GPIO1_IO20
GPIO1_IO21
UART2_RX
UART2_TX
UART2_RTS_B
UART2_CTS_B
UART5_TX
UART4_RX
Select: UART | GPIO
UART4_TX
UART5_RX
GPIO1_IO23
GPIO1_IO22
GPIO1_IO30
GPIO1_IO29
GPIO1_IO28
GPIO1_IO31
